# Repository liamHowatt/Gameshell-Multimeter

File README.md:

# GameShell Multimeter
This project is documented on the GameShell forum so that it can gain attention from the GameShell community.

Find the writeup here:  
https://forum.clockworkpi.com/t/gameshell-multimeter-project/5875

---

<br />This work is licensed under a <a rel="license" href="http://creativecommons.org/licenses/by/4.0/">Creative Commons Attribution 4.0 International License</a>.

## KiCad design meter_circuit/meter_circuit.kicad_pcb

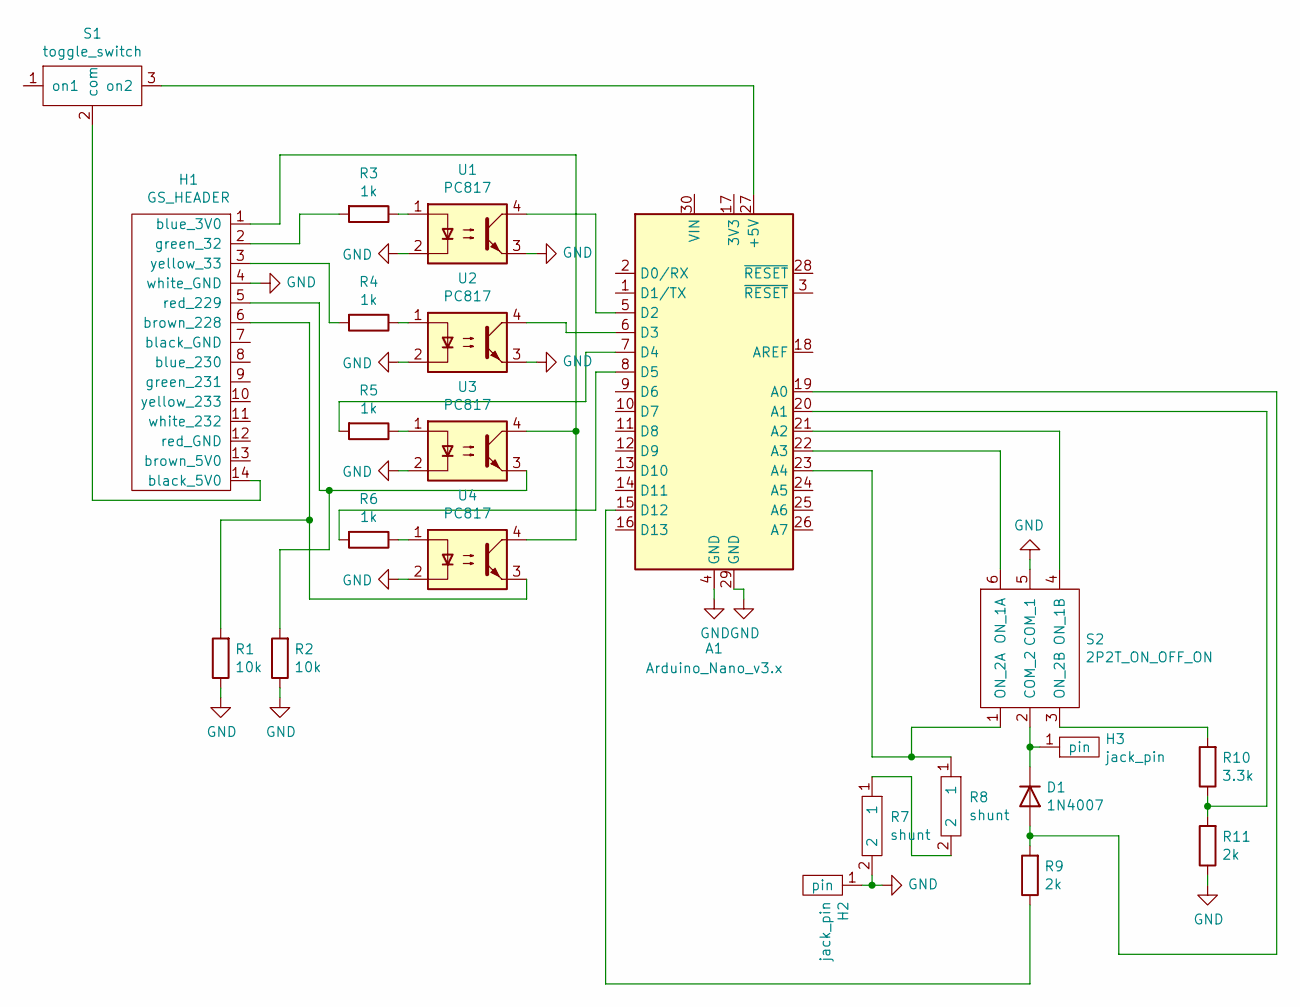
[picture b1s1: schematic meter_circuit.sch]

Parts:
A1: Arduino_Nano_v3.x; Arduino_Nano
D1: 1N4007; D_DO-41_SOD81_P10.16mm_Horizontal
H1: GS_HEADER; GSbus
H2, H3: jack_pin
R1, R2: 10k; R_Axial_DIN0207_L6.3mm_D2.5mm_P10.16mm_Horizontal
R3, R4, R5, R6: 1k; R_Axial_DIN0207_L6.3mm_D2.5mm_P10.16mm_Horizontal
R7, R8: shunt; 1W2shunt
R9, R11: 2k; R_Axial_DIN0207_L6.3mm_D2.5mm_P10.16mm_Horizontal
R10: 3.3k; R_Axial_DIN0207_L6.3mm_D2.5mm_P10.16mm_Horizontal
S1: toggle_switch
S2: 2P2T_ON_OFF_ON; 2p2t
U1, U2, U3, U4: PC817; DIP-4_W7.62mm

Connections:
GND: A1.4 (GND), A1.29 (GND), H1.4 (white_GND), H2.1, R1.1, R2.1, R7.2, R11.1, S2.5 (COM_1), U1.2, U1.3, U2.2, U2.3, U3.2, U4.2
unnamed: A1.5 (D2), U1.4
unnamed: A1.6 (D3), U2.4
unnamed: A1.7 (D4), R5.2
unnamed: A1.8 (D5), R6.2
unnamed: A1.15 (D12), R9.1
unnamed: A1.19 (A0), D1.2 (A), R9.2
unnamed: A1.20 (A1), R10.1, R11.2
unnamed: A1.21 (A2), S2.4 (ON_1B)
unnamed: A1.22 (A3), S2.6 (ON_1A)
unnamed: A1.23 (A4), R8.1, S2.1 (ON_2A)
unnamed: A1.27 (+5V), S1.3 (on2)
unnamed: D1.1 (K), H3.1, S2.2 (COM_2)
unnamed: H1.1 (blue_3V0), U3.4, U4.4
unnamed: H1.2 (green_32), R3.2
unnamed: H1.3 (yellow_33), R4.2
unnamed: H1.5 (red_229), R2.2, U3.3
unnamed: H1.6 (brown_228), R1.2, U4.3
unnamed: H1.14 (black_5V0), S1.2 (com)
unnamed: R3.1, U1.1
unnamed: R4.1, U2.1
unnamed: R5.1, U3.1
unnamed: R6.1, U4.1
unnamed: R7.1, R8.2
unnamed: R10.2, S2.3 (ON_2B)

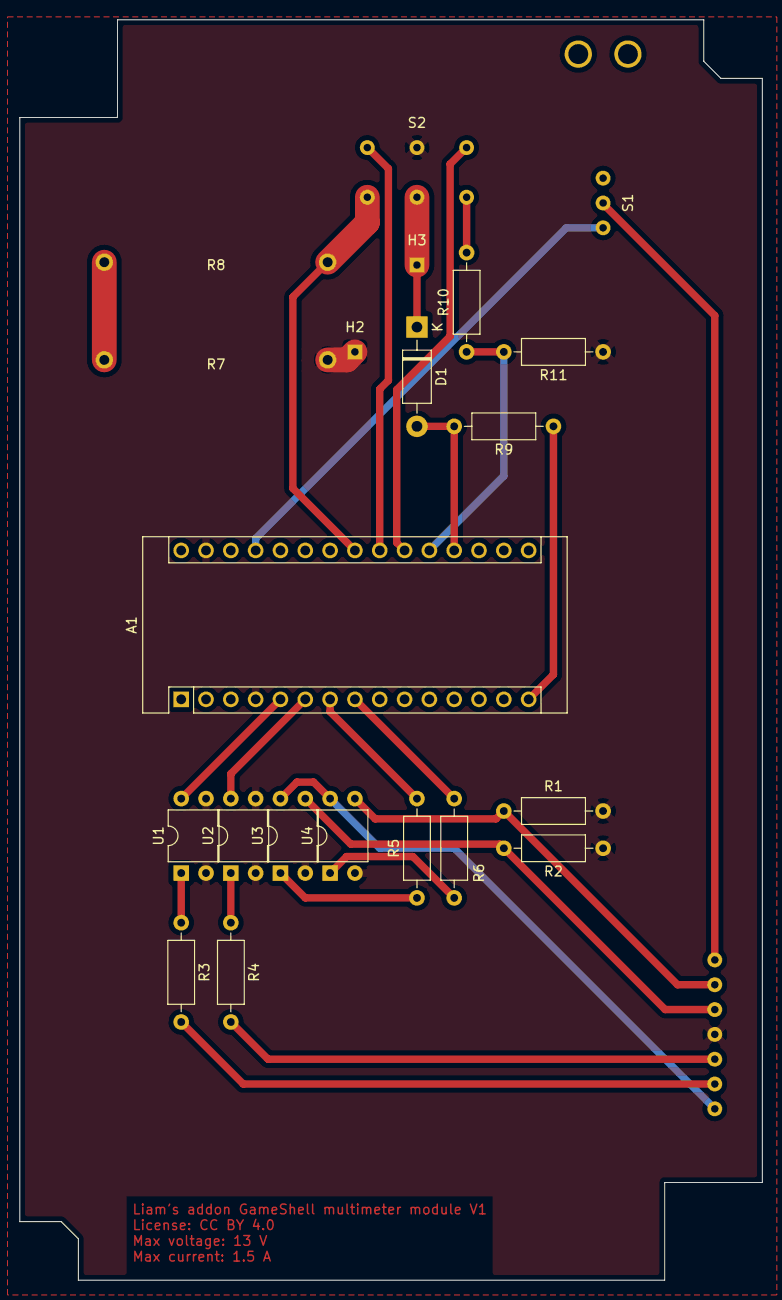
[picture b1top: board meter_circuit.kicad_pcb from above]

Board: 2 copper layers, 76.0 x 129.0 mm, 22 parts (1 on the bottom side), 25 nets.

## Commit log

2020-09-08 added KiCAD files

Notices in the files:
meter_circuit/meter_circuit.kicad_pcb:
License: CC BY 4.0
